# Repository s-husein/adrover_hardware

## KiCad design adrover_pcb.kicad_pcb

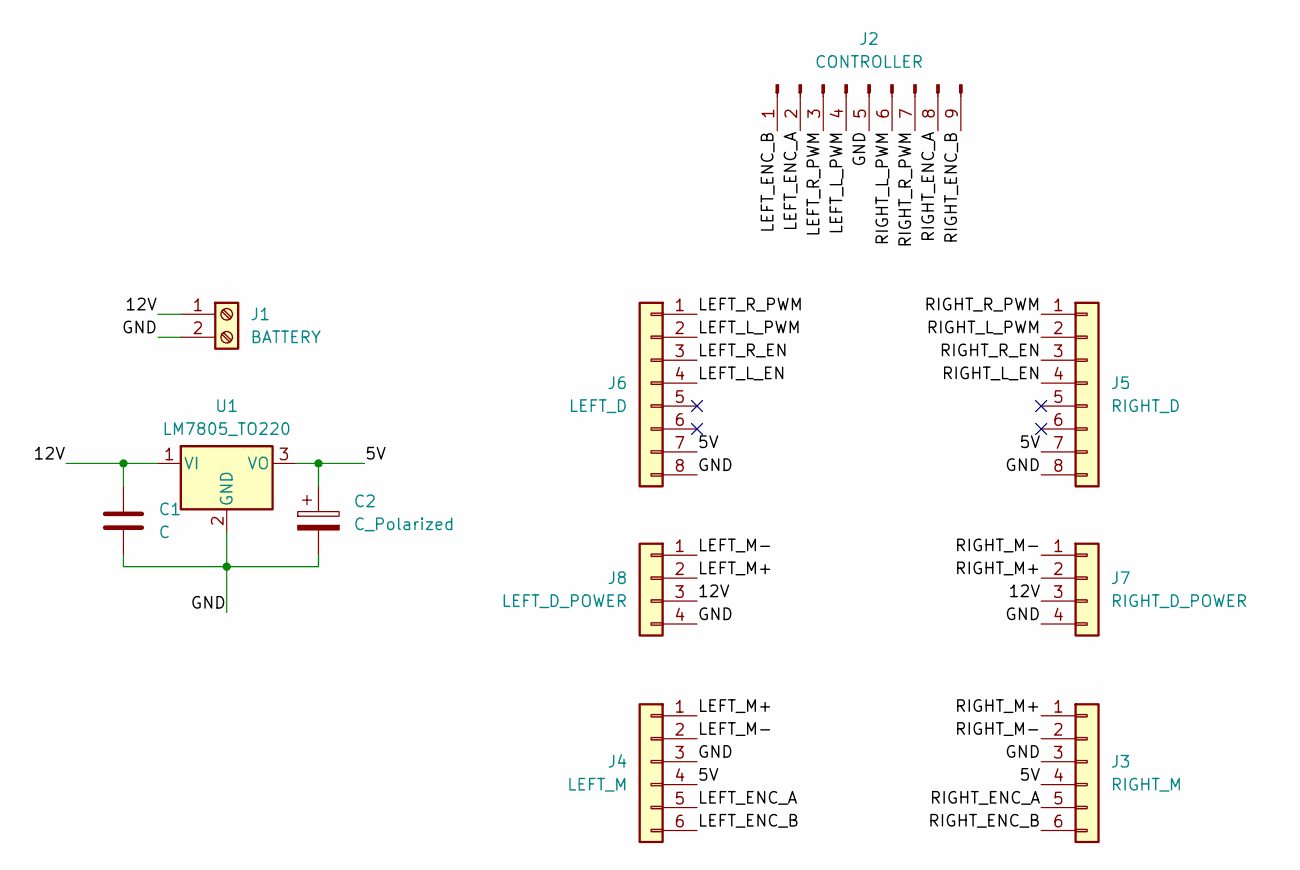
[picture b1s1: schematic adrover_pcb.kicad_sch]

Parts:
C1: C; CP_Radial_D5.0mm_P2.50mm
C2: C_Polarized; CP_Radial_D5.0mm_P2.50mm
J1: BATTERY; TerminalBlock_bornier-2_P5.08mm
J2: CONTROLLER; PinHeader_1x09_P2.54mm_Vertical
J3: RIGHT_M; PinSocket_1x06_P2.54mm_Vertical
J4: LEFT_M; PinSocket_1x06_P2.54mm_Vertical
J5: RIGHT_D; PinSocket_2x04_P2.54mm_Vertical
J6: LEFT_D; PinSocket_2x04_P2.54mm_Vertical
J7: RIGHT_D_POWER; TerminalBlock_bornier-4_P5.08mm
J8: LEFT_D_POWER; TerminalBlock_bornier-4_P5.08mm
U1: LM7805_TO220; TO-220-3_Vertical

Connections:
/5V: C2.1, J3.4, J4.4, J5.7, J6.7, U1.3 (VO)
/12V: C1.1, J1.1, J7.3, J8.3, U1.1 (VI)
/GND: C1.2, C2.2, J1.2, J2.5, J3.3, J4.3, J5.8, J6.8, J7.4, J8.4, U1.2 (GND)
/LEFT_ENC_A: J2.2, J4.5
/LEFT_ENC_B: J2.1, J4.6
/LEFT_L_EN: J6.4
/LEFT_L_PWM: J2.4, J6.2
/LEFT_M+: J4.1, J8.2
/LEFT_M-: J4.2, J8.1
/LEFT_R_EN: J6.3
/LEFT_R_PWM: J2.3, J6.1
/RIGHT_ENC_A: J2.8, J3.5
/RIGHT_ENC_B: J2.9, J3.6
/RIGHT_L_EN: J5.4
/RIGHT_L_PWM: J2.6, J5.2
/RIGHT_M+: J3.1, J7.2
/RIGHT_M-: J3.2, J7.1
/RIGHT_R_EN: J5.3
/RIGHT_R_PWM: J2.7, J5.1

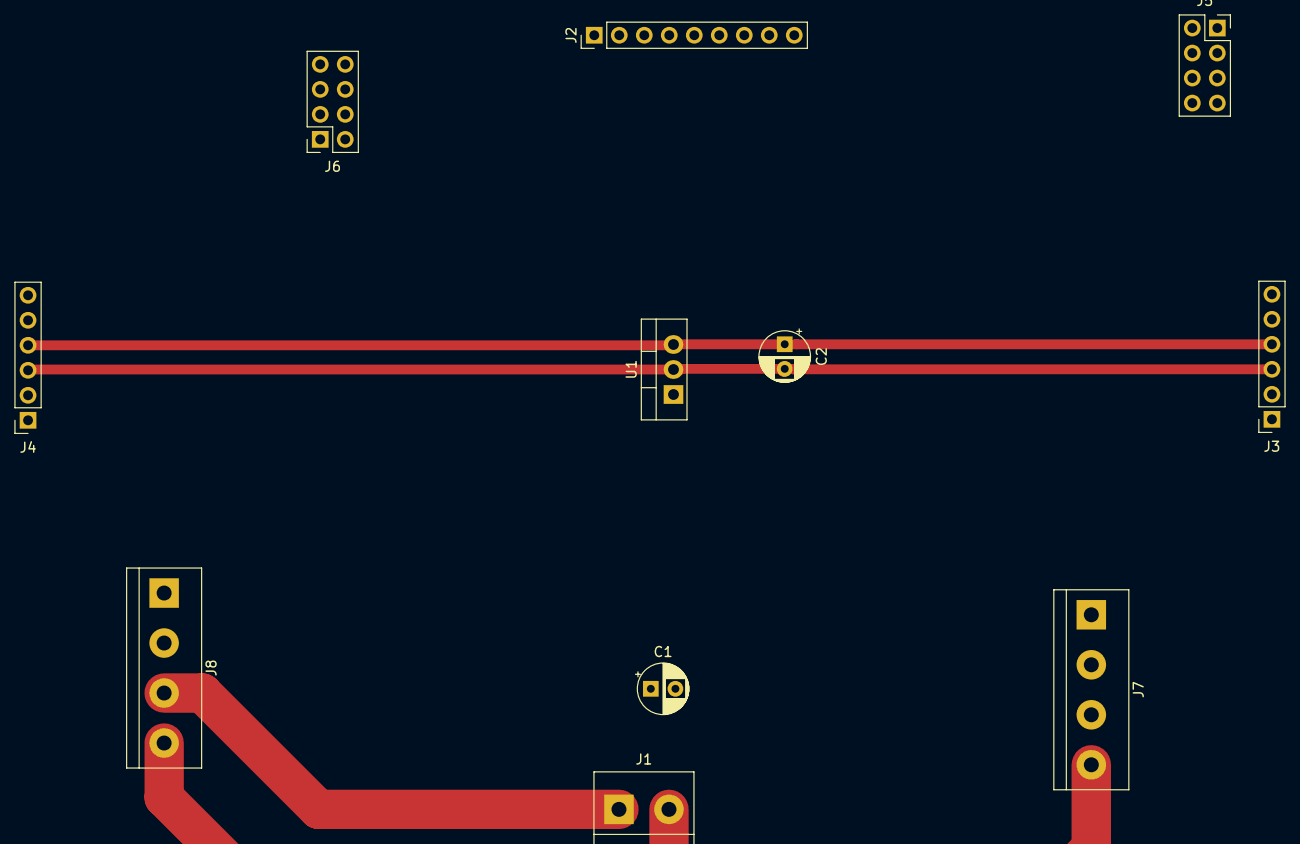
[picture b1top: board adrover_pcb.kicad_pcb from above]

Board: 2 copper layers, 11 parts (0 on the bottom side), 15 nets.
